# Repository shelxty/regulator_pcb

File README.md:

# 5V to 3.3V TPS79333 Regulator Board

After a lot of struggle with attempting to understand KiCad (thank you Hack Club Fallout mentors!) I made a simple linear voltage regulator to get started with learning, since this was a project simple enough to actually understand completely (schematic, PCB, everything). It's the first PCB I fully finished, designed in KiCad. I guess it can also be counted as my first actual electronics project! 

This is a tiny breakout board that takes unregulated input voltage (anywhere between around 3.4V to 5V) and outputs clean, fixed 3.3V volts. 

## Custom Features
- **Two LEDs:** This board has a red LED that lights up when input power is applied, and a green LED that confirms the output rail is working and regulating the voltage.
- **Feed-forward capacitor (C3):** On the feedback path, a feed-forward capacitor is set to improve noise rejection.
- **Compactness:** Each part has a footprint of 0805 or smaller, meaning this regulator board is extremely tiny and portable.

...and a very bad drawing I impulsively drew.

## How the Circuit Works (w/ Labels)
| Label | Part | What it Does |
|--------|-------|------------|
| U1 | TPS79333 | The actual regulator, which drops the input voltage to a fixed output of 3.3V | 
| J1 | 2-pin connector | The power input (it takes in unregulated voltage), with a ground pin | 
| J2 | 2-pin connector | The power output (outputs a regulated 3.3V), with a ground pin | 
| C2 | 2.2uF capacitor | Input decoupler (it smoothes out incoming supply before it gets to the regulator) | 
| C1 | 0.1uF capacitor | Output decoupler (keeps the 3.3V rail stable should turbulence arise) | 
| C3 | 0.01uF capacitor | Feed-forward capacitor (improves noise rejection, according to the TI reference design) | 
| R2 | 280Ω resistor | Causes a 1.9V drop (3.3V - 1.9V) / 5mA = 280Ω | 
| R1 | 649Ω resistor | Causes a 1.75V drop (5 - 1.75V) / 5mA = 650Ω | 
| D1 | Red LED | Lights up when input voltage is applied | 
| D2 | Green LED | Lights up when 3.3V voltage is successfully outputted | 

## PCB Design 
This small regulator board is a 2 layer PCB with 2 sets of connectors. 

_PCB Editor View_

_Schematic Editor View (w/ comments & text for beginners to understand because I'm a complete beginner)_

## Bill of Materials 

|Item	|Description|	Reference	|Qty	|MOQ|	Value|	Unit Price ($)|	Total Price ($)	|Footprint|	MPN	|URL|
|-----|-----|-----|-----|-----|-----|-----|-----|-----|-----|-----|
|Capacitor	|Output decoupler|	C1|	1|	25	|0.1uF|	0.0061|	0.15|	Capacitor_SMD:C_0805_2012Metric|	C0805B104K500NT	|[Link](https://www.lcsc.com/product-detail/C476766.html?spm=wm.fly.bg.5.xh___wm.fly.tp.3.ml&lcsc_vid=QQVaAVJeTlJdUVBVE1hcBVFWEwcNBVxeQwAPA1YHFQMxVlNeRlhXVlNWQFReUjsOAxUeFF5JWBYZEEoKFBINSQcJGk4NBhADEA4cHktXRlVcSQwSGg0%3D)|
|Capacitor	|Input decoupler|	C2	|1|	10|	2.2uF|	0.024|	0.24|	Capacitor_SMD:C_0805_2012Metric|	CL21B225KAFNNNE|	[Link](https://www.lcsc.com/product-detail/C19110.html?spm=wm.fly.bg.0.xh___wm.fly.tp.3.ml&lcsc_vid=QQVaAVJeTlJdUVBVE1hcBVFWEwcNBVxeQwAPA1YHFQMxVlNeRlhXVlNWQFReUjsOAxUeFF5JWBYZEEoKFBINSQcJGk4NBhADEA4cHktXRlVcSQwSGg0%3D)|
|Capacitor|	Feed-forward capacitor|	C3|	1|	50|	0.01uF|	0.0094|	0.47|	Capacitor_SMD:C_0805_2012Metric|	CL21B103KBANNNC|	[Link](https://www.lcsc.com/product-detail/C1710.html?spm=wm.fly.bg.0.xh___wm.fly.tp.3.ml&lcsc_vid=QQVaAVJeTlJdUVBVE1hcBVFWEwcNBVxeQwAPA1YHFQMxVlNeRlhXVlNWQFReUjsOAxUeFF5JWBYZEEoKFBINSQcJGk4NBhADEA4cHktXRlVcSQwSGg0%3D) |
|Red & green LEDs|	Lights up upon input|	D1,D2|	1|	100|  LED-RED,LED-GREEN|	0.0143|	1.43|	LED_SMD:LED_0805_2012Metric	|	| [Link](https://www.aliexpress.us/item/3256812235321424.html?spm=a2g0o.productlist.main.9.40ff6dfeufImUM&algo_pvid=1b22d9b3-163a-48fe-a597-e316fd92717e&algo_exp_id=1b22d9b3-163a-48fe-a597-e316fd92717e-8&pdp_ext_f=%7B%22order%22%3A%227%22%2C%22eval%22%3A%221%22%2C%22fromPage%22%3A%22search%22%7D&pdp_npi=6%40dis%21USD%214.08%211.43%21%21%2127.52%219.65%21%402101d9ef17819931688657801eb4d5%2112000058343268106%21sea%21US%217756416958%21X%211%210%21n_tag%3A-29911%3Bd%3A882c3b75%3Bm03_new_user%3A-29895%3BpisId%3A5000000208226559&curPageLogUid=dpkon91Z9mo7&utparam-url=scene%3Asearch%7Cquery_from%3A%7Cx_object_id%3A1005012421636176%7C_p_origin_prod%3A)|
| 2-pin connector|	Power input/output	|J1,J2|	2|	10|	Conn_01x02|	0.0191	|1.91|	Connector_PinHeader_2.54mm:PinHeader_1x02_P2.54mm_Vertical|	|	[Link](https://www.aliexpress.us/item/3256807253955994.html?spm=a2g0o.productlist.main.2.2e9b62b2mTT3WZ&algo_pvid=93b7913f-9a4f-483d-99ae-aac3188ba0c6&algo_exp_id=93b7913f-9a4f-483d-99ae-aac3188ba0c6-1&pdp_ext_f=%7B%22order%22%3A%22789%22%2C%22eval%22%3A%221%22%2C%22fromPage%22%3A%22search%22%7D&pdp_npi=6%40dis%21USD%216.83%211.91%21%21%2146.07%2112.86%21%40210328d417819933313278739edf81%2112000040762755700%21sea%21US%217756416958%21X%211%210%21n_tag%3A-29911%3Bd%3A882c3b75%3Bm03_new_user%3A-29895%3BpisId%3A5000000209180939&curPageLogUid=T0dEK33dI0p0&utparam-url=scene%3Asearch%7Cquery_from%3A%7Cx_object_id%3A1005007440270746%7C_p_origin_prod%3A) | 
|Resistor|	649 Ohms|	R1|	1|100|		649|	0.001|	0.1|	Resistor_SMD:R_0805_2012Metric|	HRC0805F6490FNTN|	[Link](https://www.lcsc.com/product-detail/C55098624.html?s_z=n_q_t_resistor&spm=wm.fly.bg.5.xh___wm.ssy.tc.0.tz&lcsc_vid=QQVaAVJeTlJdUVBVE1hcBVFWEwcNBVxeQwAPA1YHFQMxVlNeRlhXVFBXQVJaVTsOAxUeFF5JWBYZEEoKFBINSQcJGk4eAhYVGA8PCycDGRULFUsLDjEcCA4DFBVBAwESFggC) | 
| Resistor|	280 Ohms|	R2|	1|	100|	280|	0.0031|	0.31|	Resistor_SMD:R_0805_2012Metric|	FRC0805F2800TS|	[Link](https://www.lcsc.com/product-detail/C2960739.html?s_z=n_q_t_resistor&spm=wm.fly.bg.0.xh___wm.ssy.tc.0.tz&lcsc_vid=QQVaAVJeTlJdUVBVE1hcBVFWEwcNBVxeQwAPA1YHFQMxVlNeRlhXVFBXQVJaVTsOAxUeFF5JWBYZEEoKFBINSQcJGk4eAhYVGA8PCycDGRULFUsLDjEcCA4DFBVBAwESFggC) |
| TPS79333|	Regulator|	U1|	1|	5|	TPS79333-EP	|0.3|	1.52|	Package_TO_SOT_SMD:SOT-23-5|	TPS79333DBVR|	[Link](https://www.lcsc.com/product-detail/C9840.html?s_z=n_q_TPS79333&spm=wm.fly.bg.1.xh&lcsc_vid=QQVaAVJeTlJdUVBVE1hcBVFWEwcNBVxeQwAPA1YHFQMxVlNeRlhXVFNXRlNYVzsOAxUeFF5JWBYZEEoKFBINSQcJGk4eFQsCAgIaSgADAwAHC0slQlReXlxQRVVADxALGw%3D%3D) | 
| PCB Fabrication | Producing PCB from JLCPCB | |  1 | | | 2.2 | 2.2 | | | |
| PCB Fabrication | Producing PCB from JLCPCB | |  1 | | | 3.12 | 3.12 | | | |
| **Total**|  |  | 			**11**	|  |  |  |			**11.45**  | 

----

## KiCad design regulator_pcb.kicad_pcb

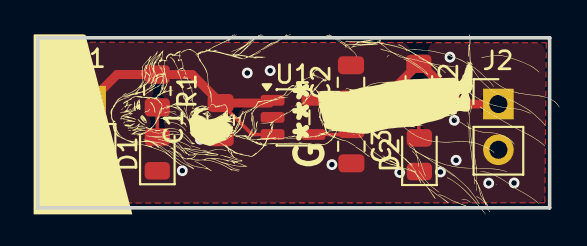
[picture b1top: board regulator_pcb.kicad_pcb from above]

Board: 2 copper layers, 28.4 x 9.4 mm, 10 parts (0 on the bottom side), 6 nets.

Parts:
C1: 0.1uF; C_0805_2012Metric
C2: 2.2uF; C_0805_2012Metric
C3: 0.01uF; C_0805_2012Metric
D1: LED-RED; LED_0805_2012Metric
D2: LED-GREEN; LED_0805_2012Metric
J1, J2: Conn_01x02; PinHeader_1x02_P2.54mm_Vertical
R1: 649; R_0805_2012Metric
R2: 280; R_0805_2012Metric
U1: TPS79333-EP; SOT-23-5

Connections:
GND: C1.2, C2.2, C3.2, D1.1 (K), D2.1 (K), J1.2, J2.2, U1.2 (GND)
unnamed: D1.2 (A), R1.2
unnamed: D2.2 (A), R2.2
unnamed: C1.1, J1.1, R1.1, U1.1 (IN), U1.3 (EN)
unnamed: C2.1, J2.1, R2.1, U1.5 (OUT)
unnamed: C3.1, U1.4 (BP)

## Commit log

2026-06-18 test1
2026-06-19 finished schematic, almost done with pcb
2026-06-19 finished copper fill and got everything drc-verified!
2026-06-19 drawing
2026-06-20 Update README with project details and features
    Added detailed project description, features, and circuit explanation.
2026-06-20 Add Bill of Materials section to README
2026-06-20 added zine
2026-06-20 added bom
2026-06-20 Rename BOM_regulator_pcb.csv to BOM.csv
2026-06-21 uploaded zine
2026-06-24 Create test
2026-06-24 Rename regulator_pcb.kicad_pcb to pcb/regulator_pcb.kicad_pcb
2026-06-24 moving files asdfasdf
2026-06-24 Update BOM.csv with new items and quantities
2026-06-24 Revise component table and include PCB fabrication costs
    Updated component list and added PCB fabrication details.
2026-06-24 added in updated zine
    yes, i measured the blue and red space! although it looks a little messy like this, my name, the qr code, and everything else fits perfectly within the borders!
    canva link if needed: https://canva.link/35jp8b346m9nq27
2026-06-25 gerbers
    gerb
2026-06-25 Rename gerbers.zip to productions/gerbers.zip
2026-06-25 Adjust PCB fabrication cost and total in README
    Updated PCB fabrication costs in the bill of materials.
2026-06-25 Update BOM.csv with new item entries and totals
2026-06-25 Revise BOM with updated component details
    Updated BOM.csv to reflect new pricing and quantities for components.
